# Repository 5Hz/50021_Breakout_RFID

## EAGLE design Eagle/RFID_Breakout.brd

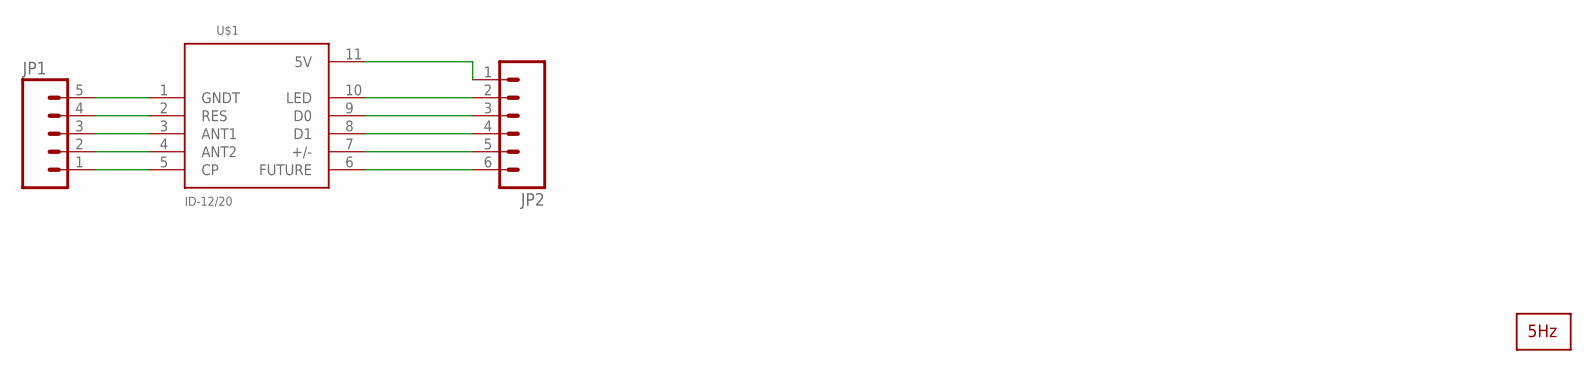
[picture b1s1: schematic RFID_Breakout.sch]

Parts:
JP1: M05PTH; 1X05
JP2: M06SIP; 1X06
U$1: ID-12/20; ID-12
U$2: LOGO2_SILK5MM; LOGO2_5MM

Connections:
5V: JP2.1, U$1.11 (5V)
+/-: JP2.5, U$1.7 (+/-)
ANT1: JP1.3, U$1.3 (ANT1)
ANT2: JP1.2, U$1.4 (ANT2)
CP: JP1.1, U$1.5 (CP)
D0: JP2.3, U$1.9 (D0)
D1: JP2.4, U$1.8 (D1)
FUTURE: JP2.6, U$1.6 (FUTURE)
GND: JP1.5, U$1.1 (GNDT)
LED: JP2.2, U$1.10 (LED)
RES: JP1.4, U$1.2 (RES)

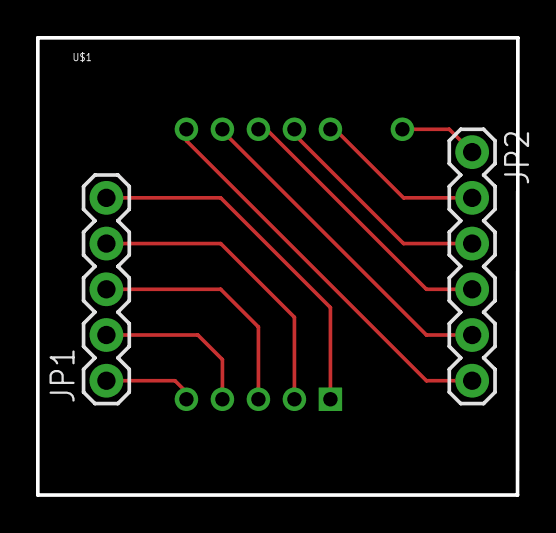
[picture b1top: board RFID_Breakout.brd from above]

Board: 2 copper layers, 26.7 x 25.4 mm, 4 parts (1 on the bottom side), 11 nets.

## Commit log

2014-01-10 creación

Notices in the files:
parts and their libraries:
SparkFun: Licensing: CC v3.0 Share-Alike You are welcome to use this library for commercial purposes.
